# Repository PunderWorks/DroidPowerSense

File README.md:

# DroidPowerSense

An inline battery power switch, protection and telemetry board for droid builds. It sits between the
battery and the rest of the droid, switches the main power from a small remote switch, protects the
droid's electronics, and reports battery voltage and current over CAN FD and UART.

## What it does

- **Power switch with zero drain.** Back-to-back MOSFETs under an LM5060 controller switch up to
  30 A continuous (60 A peak). A small remote switch turns the droid on and off;
  with the switch off, the fitted battery draws nothing beyond semiconductor leakage (< 1 µA).
- **Works with common droid batteries:** 9-32 V, for example 12 V lead-acid, 18 V / 20 V Max
  power-tool packs, and 24 V LiPo / LiFePO4.
- **Protection:** reverse battery, input and output surge (TVS), motor flyback, under- and
  over-voltage cutoff, and an overcurrent / short-circuit trip. The turn-on is soft-started so large
  motor-controller capacitors don't cause a current spike.
- **Telemetry:** battery voltage (readable even with the load switched off), load voltage and
  current (±164 A range, 5 mA resolution), reported over **CAN FD** (daisy-chainable) and a
  level-shifted **UART** (3.3 V or 5 V).
- **Lit remote switches:** supports plain switches and switches with a built-in light that is on
  whenever the droid is on. Firmware can blink it.
- **Two-circuit droids:** a circuit ID jumper lets two boards (one per circuit) identify themselves.
- **Serviceable:** the ESP32-C5 module plugs into sockets and programs over its own USB-C.

## How it fits in a droid

```
Battery ── XT60 lead with in-line blade fuse (30 A) ─▶ BAT IN [ DroidPowerSense ] LOAD OUT ─▶ droid fuse box ── motor controllers / electronics
                                                          │      │     │
                                         remote switch ───┘      │     └── CAN FD in / out (daisy chain)
                                                                 └──────── UART (3.3 V or 5 V)
```

- **Use an XT60 battery lead with an in-line blade fuse** (a common off-the-shelf part) between the
  battery and BAT IN: **30 A** for most builds, 40 A at most. The board is an electronic circuit
  breaker, not a current limiter, so only a fuse clears a dead short quickly. Fused at the battery,
  everything after it is covered: the battery lead, the board, and the remote-switch lead.
- **Wire the remote switch with 22 AWG or heavier.** Its `BAT+` wire carries battery voltage, so a
  chafed lead must draw enough current to blow the battery fuse before the wire overheats; 26 AWG can
  melt first.
- A fuse box for the droid's branch circuits can go after LOAD OUT as usual.
- Up to **4.7 mF** of capacitance on LOAD OUT at 32 V (more at lower battery voltages).
- One board per power circuit.

## Specifications

| | |
|---|---|
| Input voltage | 9-32 V (hardware under-voltage cutoff ≈ 7.5 V, over-voltage cutoff ≈ 38 V) |
| Current | 30 A continuous, 60 A peak |
| Power connectors | XT60PW-M in (mates with the battery's female XT60), XT60PW-F out |
| Off-state drain | < 1 µA with the remote switch open |
| Current / voltage sensing | TI INA237 on a 1 mΩ shunt: ±164 A range, 5 mA resolution; also measures the LOAD OUT voltage |
| Battery voltage sensing | ESP32-C5 ADC through a ÷ 11 divider |
| MCU | Waveshare ESP32-C5-Zero-M (Wi-Fi 6, BLE 5, CAN FD), on 2.54 mm sockets |
| Comms | CAN FD (TI TCAN334G, 2 × 3-pin JST-XH with bus ground, jumper termination); UART (3-pin JST-XH with ground, 3.3 V / 5 V) |
| Board | 76 × 58 mm, 4 layers, 1.6 mm, 1 oz copper, components on one side |
| Mounting | 4 × M3 holes |

## Connectors and jumpers

Every connector has its pin functions printed on the board next to each pin.

| Ref | Silkscreen | Type | Pins / settings |
|---|---|---|---|
| J1 | BAT IN | XT60PW-M | + / − from the battery, through the in-line fused XT60 lead |
| J2 | LOAD OUT | XT60PW-F | + / − to the droid |
| J3 | REMOTE SW | JST-XH 4-pin | `BAT+`, `SW`, `LED-`, `LED+` (see below) |
| J5 / J6 | CAN IN / CAN OUT | JST-XH 3-pin | `GND`, `CANL`, `CANH`; wired in parallel, so IN and OUT are a cabling convention. `GND` is a bus ground reference: run it through every CAN cable |
| J8 | UART | JST-XH 3-pin | `GND`, `RX` (into the board), `TX` (out of the board). Connect `GND` to the other device's ground |
| J7 | TERM | 2-pin jumper | Fitted = 120 Ω CAN termination. Fit only on the boards at the two ends of the bus. |
| J9 | UART V | 3-pin jumper | `3V3`-`UART` = 3.3 V UART; `UART`-`5V` = 5 V UART |
| J4 | CIRCUIT ID | 2-pin jumper | No jumper = circuit 1, jumper on = circuit 2 |

The three jumper shunts (Würth 60900213421) are in the BOM.

The CAN and UART `GND` pins are signal references, not power returns: each goes to the board's
ground through a resettable fuse (PTC), so if a battery-negative lead comes off while a comms cable
is still plugged in, the fuse trips instead of the load current flowing through the thin comms wire.
Always connect battery negative through the XT60s.

### Wiring the remote switch (J3)

| J3 pin | Plain switch | Lit switch, 3-terminal (+ / ACC / GND) | Lit switch, separate LED terminals |
|---|---|---|---|
| `BAT+` | one side | + | one contact |
| `SW` | other side | ACC (output) | other contact |
| `LED-` | — | GND | LED − |
| `LED+` | — | — | LED + |

- **3-terminal lit switches** power their light from the battery, so buy one rated for your pack
  (12 V for lead-acid; 24 V or "12-24 V" for 18-24 V packs).
- **Switches with separate LED terminals:** buy the **5 V or 6 V** LED version. The board powers it
  from its own 5 V, so the same switch works on any battery.

## Before you power it up

- **Fuse the battery lead:** an XT60 lead with an in-line blade fuse (30 A, 40 A max) ahead of
  BAT IN, and 22 AWG or heavier for the remote-switch lead.
- **Heatsink for high continuous current:** typical droid loads (under about 1 A average, with
  short motor peaks) need none. For continuous loads above about 15 A, fit a small stick-on
  heatsink to the marked area on the back, but **only with an electrically insulating thermal pad**. Bare
  metal would short the power nets underneath and bypass the switch.
- **Secure the module** in a droid that vibrates: a dab of hot glue or a cable tie at the antenna end.
  It stands about 11 mm tall on its sockets.
- **Firmware is part of the protection.** Overcurrent cutoff between 30 A and the hardware trip
  point, and never cutting power while the motors are regenerating, are firmware's job; see
  [docs/firmware-requirements.md](docs/firmware-requirements.md).

## Project status

| Area | Status |
|---|---|
| Hardware design | Complete and reviewed: all design and layout checks pass, power stage verified in simulation |
| PCB | v1.0 routed and reviewed for fab: 76 × 58 mm on 4 layers (moved from 70 × 50 mm on 6 layers, cheaper to fab) with 3-pin CAN/UART connectors. DRC and all design checks clean; fab files in [`PCB/production/`](PCB/production/). The renders above are of the earlier 6-layer layout until they are re-rendered. |
| Firmware | Not started (Rust on the ESP32-C5). Requirements captured in [docs/firmware-requirements.md](docs/firmware-requirements.md). |
| Bench testing | Not started. The first-board checklist is in [PCB/README.md](PCB/README.md#bench-checklist-first-board). |

## Repository layout

| Path | Contents |
|---|---|
| [`PCB/README.md`](PCB/README.md) | Hardware design: requirements, circuit, decisions, layout, accepted risks and bench checklist |
| [`PCB/stackup/`](PCB/stackup/) | The electrical design in [Stackup](https://github.com/stackup-eda/stackup) KDL (`board.kdl`, `parts.kdl`); there are no KiCad schematics |
| `PCB/DroidPowerSense.kicad_pcb` | The KiCad 10 board, synced from the Stackup design |
| [`PCB/production/`](PCB/production/) | Fab files: Gerbers and drills, purchasing BOM, placement file |
| [`PCB/datasheets/`](PCB/datasheets/) | Manufacturer datasheets, with source and hash in `manifest.json` |
| [`PCB/libraries/`](PCB/libraries/) | Custom footprints and 3D models (XT60PW, socketed ESP32 module) |
| [`scripts/spice/`](scripts/spice/README.md) | ngspice simulations of the power switch and UART level shifters, and an SOA checker |
| [`docs/firmware-requirements.md`](docs/firmware-requirements.md) | What the firmware must do for the hardware, pin map and peripheral setup |
| `ci/` | The pinned Stackup CLI and the PCB sync check used by CI |
| `src/` | Firmware (Rust, ESP32-C5), not started yet |

## Working on the design

The design is checked with the Cargo-pinned Stackup CLI and KiCad 10 (`kicad-cli`):

```sh
cargo run --locked --manifest-path ci/stackup/Cargo.toml -- check PCB/stackup/board.kdl --locked
python3 scripts/spice/power_switch_sim.py     # power switch, all scenarios
python3 scripts/spice/uart_shifter_sim.py     # UART level shifters
python3 scripts/spice/test_soa.py             # SOA checker unit tests
```

- After any change to the KDL, sync the PCB from Stackup (see [PCB/README.md](PCB/README.md)) and
  commit the board with the KDL. CI fails if they drift apart.
- Refill the pours and regenerate `PCB/production/` after any board change; the commands are in
  [PCB/README.md](PCB/README.md).
- Changes go through pull requests; history is kept linear (rebase merges).

## Ordering

- **Fab:** 4 layers, 1.6 mm, 1 oz copper; minimum track and spacing 0.2 mm. 2 oz outer copper
  roughly doubles the price and isn't needed for typical droid loads; see
  [PCB/README.md](PCB/README.md) for the trade-off.
- **Parts:** the BOM lists Mouser and DigiKey numbers (LCSC where available). The XT60 connectors
  (Amass) and the ESP32-C5-Zero-M module (Waveshare) come from their own channels.
- **Hand assembly:** the connectors, jumpers, module sockets and module are through-hole and
  hand-soldered; the placement file lists only the 69 surface-mount parts.

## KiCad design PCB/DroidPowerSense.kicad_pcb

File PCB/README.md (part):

# DroidPowerSense hardware

The electrical design is Stackup KDL in [`stackup/`](stackup/) (`board.kdl`, plus the local parts in
`parts.kdl`). The KiCad board `DroidPowerSense.kicad_pcb` is synced from it through
`DroidPowerSense.stackup_sch`. Manufacturer datasheets are in [`datasheets/`](datasheets/), with
their source URLs and hashes in `datasheets/manifest.json`.

```sh
stackup check PCB/stackup/board.kdl --locked     # check the design
stackup bom PCB/stackup/board.kdl --locked -o bom.csv
python3 scripts/spice/power_switch_sim.py          # power-switch SPICE corners (23 checks)
```

After changing the KDL, use **Sync PCB from stackup** in KiCad's PCB editor, or sync headless with
the board closed:

```sh
/Applications/KiCad/KiCad.app/Contents/Frameworks/Python.framework/Versions/Current/bin/python3 \
  <stackup checkout>/kicad-plugin/sync_headless.py PCB/DroidPowerSense.kicad_pcb
```

Commit the synced PCB with the KDL. CI fails if syncing would change the committed PCB.

## Requirements

| Area | Requirement |
|---|---|
| Position | Inline between the battery and the droid, before its fuses. One board per circuit; droids with two circuits use two boards. |
| Batteries | 9-32 V: 12 V lead-acid, 18 V / 20 V Max power-tool packs, 24 V LiPo / LiFePO4. |
| Current | < 1 A to 30 A continuous, 60 A peak, measured in both ranges. |
| Power connectors | Polarized, high-current: XT60PW-M in (mates with the battery's female XT60), XT60PW-F out. |
| Switching | MOSFET switch so a fitted battery draws nothing while the droid is off. Switched by a remote low-power switch on a 4-pin JST-XH (switch + lit-switch LED). |
| Lit switch | Support lit-when-on switches: 3-terminal (+ / ACC / GND) and separate-LED-terminal types. The light is on whenever the board is on, firmware can blink it, and it adds no off-state drain. |
| Protection | Reverse polarity, input/output TVS, output flyback diode, over/under-voltage, overcurrent/short trip. |
| Upstream fuse | **Required:** an XT60 battery lead with an in-line blade fuse (30 A, 40 A max) ahead of J_PWR_IN, and the remote-switch lead in 22 AWG or heavier. The LM5060 is a circuit breaker with a 0.3-0.65 s fault delay, not a current limiter: only the fuse clears a dead short, and it backs up sustained overloads. |
| Overcurrent | **Firmware is the primary overload protection:** INA237 ALERT (IO4) set to the over-current limit, firmware asserts PWR_CUTOFF. The LM5060 V_DS trip (~45 A hot / ~105 A cold) is the hardware backstop; between 30 A and the trip point the hardware alone does not open the switch. |
| Load capacitance | Up to 4.7 mF on LOAD OUT at 32 V (Q1 stays within its SOA during turn-on; larger banks at 32 V exceed it). |
| MCU | ESP32-C5 (CAN FD + firmware) on a plug-in module (sockets), serviceable and programmable in place over its USB-C. Firmware in Rust. |
| Comms | CAN FD (two 3-pin JST-XH for daisy-chain, jumper termination), UART (3-pin JST-XH, 3.3 V / 5 V jumper). Pin 1 of each is a ground reference, tied to board GND through a PTC so it can never carry the load's return current. |
| Circuit ID | Firmware must tell circuit 1 from circuit 2. |
| Board | 76 × 58 mm, 4 layers, 1 oz copper, with three layers for the high-current path and a solid ground plane, components on one side. Back-side area for a user-fitted heatsink, recommended above about 15 A continuous. |
| Sourcing | Mouser and DigiKey first; LCSC numbers recorded but JLCPCB is not the planned assembler. |

## Circuit

| Block | Parts | Notes |
|---|---|---|
| Power in/out | J_PWR_IN (XT60PW-M), J_PWR_OUT (XT60PW-F), D_TVS_IN (SMCJ33CA), D_TVS_OUT (SMBJ33CA), D_FLY (B560C) | Bidirectional TVS on both sides; D_FLY clamps inductive kick from motors on the output. |
| Remote switch | J_SW (JST-XH 4-pin), D_SW (B160) | J_SW 1-2 connects VBAT_IN to VSW_CTRL. Open = the only path from the battery is TVS/MOSFET leakage (< 1 µA). D_SW blocks reverse polarity into the control rail. |
| Lit switch | J_SW.3/.4, Q_LED (BSS138), R_LED_PU 10 k | J_SW.4 = +5V for separate-terminal LEDs; J_SW.3 = LED return, switched to GND by Q_LED. R_LED_PU holds the gate on from +3V3, so the light is on as soon as the board is; IO12 low turns it off (blink). |
| High-side switch | U_PROT (LM5060), Q1/Q2 (CSD18532Q5B, back-to-back, 2.5 mΩ each), R_GATE, D_GOFF, C_GATE (100 nF 100 V), R_GATE_C (1 k), Q_REV + D_REV + R_REV | Common-source back-to-back N-FETs so the switch blocks both directions. Q_REV clamps V_GS during reverse polarity (LM5060 Fig. 41). C_GATE + R_GATE_C slows the output (~240 V/s typ) to limit inrush into capacitive loads. C_GATE is sized against the start-up timer: worst case at 32 V the gate needs 0.25 s and the timer allows 0.48 s (LM5060 IGATE 17 µA, VGATE-TH 6.5 V, ITIMERL 7 µA, VTMRH 1.70 V, ±10 % parts). 220 nF needed 0.55 s and could latch a start-up fault. |
| Protection thresholds | R_SENSE 33 k, R_OUT 10 k, C_TIMER 2.2 µF, UVLO 33 k/10 k, OVP 180 k/10 k | V_DS trip ~528 mV across 5 mΩ ≈ 105 A cold / ~45 A at 100 °C (clears 30 A continuous rating); UVLO ≈ 7.5 V rising; OVP ≈ 38 V; C_TIMER 2.2 µF: start-up window ≥ 0.48 s, V_DS fault delay 0.34 s typ / 0.65 s max. |
| MCU cutoff | Q_CUTOFF (BSS138), R_CUTOFF_PD 100 k | Firmware drives PWR_CUTOFF high to pull LM5060 EN low: load off, MCU stays powered from VSW_CTRL to report the fault. Pull-down keeps the load on through MCU boot/reset. |
| Sensing | R_SHUNT (CSS2H-2512R-1L00F, 1 mΩ 5 W), U_INA (INA237), C_INA_VS | INA237: 85 V common-mode/VBUS (VOUT reaches 42 V before D_TVS_OUT conducts, 53 V clamped; the INA226's limit was 40 V). ADCRANGE 0: ±163.84 A at 5 mA/LSB; offset ±50 mA, gain ±0.3 % max. A0/A1 to GND: I²C address 0x40. Shunt 0.9 W at 30 A, 3.6 W at 60 A (short-time overload 25 W for 5 s). Bus voltage measured on VOUT. |
| Battery ADC | R_VBAT_TOP 100 k / R_VBAT_BOT 10 k, C_VBAT_ADC | VSW_CTRL ÷ 11 into IO6, so battery voltage is readable with the MOSFETs off. |
| 5 V | U_BUCK (LMR14030, 4-40 V), R_BUCK_IN 3.3 Ω, L_BUCK 10 µH, D_BUCK (B360A) | 400 kHz, FB 56.2 k/10 k → 4.97 V. Feeds the module's 5 V pin and the UART 5 V option. R_BUCK_IN with C_BUCK_IN1/2 (BUCK_VIN) low-passes the buck input (~66 µs, ~25 µs after X5R DC-bias loss): VSW_CTRL can reach 37-53 V in an input surge, above the LMR14030's 44 V VIN/EN absolute maximum. Drop 0.76 V / 0.17 W at the worst load (0.23 A at 9 V). R_BUCK_EN pulls EN from BUCK_VIN. |
| MCU | U_MCU (Waveshare ESP32-C5-Zero-M), J_MCU_L/J_MCU_R sockets | The module plugs into two 1x9 sockets. The module's own buck makes +3V3 for the carrier (pin 3). USB-C on the module is the programming path. The module has both an onboard ceramic antenna (J2, OA-W03) and an IPEX-1/U.FL connector (J3), chosen by an RF switch on internal GPIO26 (ANT_Ctrl, 200 k pull-up to 3V3; module schematic). Firmware must drive GPIO26 to select the onboard antenna. No U.FL-free variant exists (the -M SKU only adds headers). |
| CAN FD | U_CAN (TCAN334GDR), J_CAN1/J_CAN2, R_TERM + J_TERM, F_CAN_GND | 3.3 V transceiver, normal mode (STB/SHDN internal pull-downs). Connectors: pin 1 CAN_GND, 2 CANL, 3 CANH. CAN_GND runs straight from J_CAN1 to J_CAN2 (the bus ground daisy-chains) and reaches board GND through F_CAN_GND (see Comms ground pins below). |
| UART | J_UART, J_VIO, Q_TX/Q_RX (BSS138) + pull-ups, F_UART_GND | ESP32-C5 pins are not 5 V tolerant, so both directions are level-shifted. J_UART: pin 1 UART_GND (to GND through F_UART_GND), 2 RX, 3 TX. |
| Circuit ID | J_CIRCUIT, R_CIRCUIT_PU | Open = circuit 1, shorted = circuit 2. |
| Indicator | D_PWR_LED + 1 k | On when +3V3 is up (remote switch closed). |

Jumpers: **J_VIO** (silkscreen "UART V") 1-2 = 3.3 V UART, 2-3 = 5 V UART. **J_TERM** (silkscreen "TERM")
fitted = 120 Ω terminator.
**J_CIRCUIT** no jumper = circuit 1, jumper on = circuit 2. The three shunts are in the BOM
(SH_VIO / SH_TERM / SH_CIRCUIT, Würth 60900213421) as BOM-only parts with outline-only footprints.

**Not in the BOM (user-supplied):** the heatsink (recommended above about 15 A continuous) and its electrically insulating thermal
pad (see Layout), M3 mounting hardware, and the upstream battery fuse.

Silkscreen convention: every JST connector has its pin functions printed in line with each pin
(J3 `BAT+`/`SW`/`LED-`/`LED+`, J5/J6 `CANH`/`CANL`/`GND`, J8 `GND`/`RX`/`TX`), not pin numbers. J5 is marked CAN IN and J6
CAN OUT (vertical text beside their pin labels); they are wired in parallel, so the marking is a cabling convention, not a direction the bus
needs. The labels sit over the tracks that run into each pin, which prints legibly over soldermask.

## Remote switch wiring (J3)

| J3 pin | Silkscreen | Net | Plain switch | 3-terminal lit switch (+ / ACC / GND) | Separate-LED-terminal switch |
|---|---|---|---|---|---|
| 1 | `BAT+` | VBAT_IN | one side | + | one contact |
| 2 | `SW` | VSW_RAW | other side | ACC (output) | other contact |
| 3 | `LED-` | SW_LED_K (Q_LED drain) | — | GND | LED − |
| 4 | `LED+` | +5V | — | — | LED + |

- **3-terminal switches** light their LED from the battery, so buy one rated for the pack (12 V for
  lead-acid, 24 V or "12-24 V" for 18-24 V packs). Their LED also sees the full reverse voltage if the
  battery is reversed; that relies on the switch's own protection.
- **Separate-terminal switches**: buy the **5 V or 6 V LED** version. It runs from the board's 5 V, so
  the same switch suits every battery from 12 V to 32 V.
- Battery pins (1-2) are at one end, so a slipped wire can short BAT+ to SW (just turns the board on)
  but never puts the battery on +5V.

## GPIO table (Waveshare ESP32-C5-Zero)

Firmware-side requirements (overcurrent cutoff, regen rule, INA237 setup, antenna select) are in
[docs/firmware-requirements.md](../docs/firmware-requirements.md).

| GPIO | Net | Function | Notes |
|---|---|---|---|
| IO0 | PWR_PGOOD | LM5060 nPGD (open drain) | 10 k pull-up. |
| IO1 | PWR_CUTOFF | Load cutoff | High = load off. 100 k pull-down. |
| IO2 | I2C_SDA | INA237 | 4.7 k pull-up. Strapping pin MTMS (SDIO edge only; harmless). |
| IO3 | I2C_SCL | INA237 | 4.7 k pull-up. Strapping pin MTDI (SDIO edge only; harmless). |
| IO4 | INA_ALERT | INA237 ALERT (open drain): firmware over-current cutoff | 10 k pull-up. |
| IO5 | UART_TX_3V3 | UART TX | Via Q_TX to J_UART.3. |
| IO6 | VBAT_ADC | ADC1 | Battery ÷ 11. |
| IO7 | CIRCUIT_ID | Input | 10 k pull-up. Strapping pin for JTAG source, only read if EFUSE_JTAG_SEL_ENABLE is burnt (default not). |
| IO8 | CAN_TX | TWAI/CAN FD TX | |
| IO9 | CAN_RX | TWAI/CAN FD RX | |
| IO10 | UART_RX_3V3 | UART RX | Via Q_RX from J_UART.2. |
| IO11 | — | U0TXD | Left free for the ROM boot log. |
| IO12 | SW_LED_EN | Lit-switch LED (Q_LED gate) | 10 k pull-up: light on by default; drive low to blink. U0RXD, not a strapping pin (ESP32-C5 datasheet p. 27); input with weak pull-up at reset (p. 20). The J_UART port is unaffected: it uses UART1 on IO5/IO10. |
| IO13/IO14 | — | USB D-/D+ | Module USB-C. |

## Layout

**76 × 58 mm**, 4 layers (F.Cu parts and routing / In1.Cu solid GND / In2.Cu power pours, +3V3 pour
and VSW_CTRL routing / B.Cu heatsink copper, GND and short routes), all parts on the top side.
`scripts/layout_4layer.py` converted the hand-placed 70 × 50 mm 6-layer layout: it moved parts and
silkscreen by region, rebuilt the outline, pours and stitching vias, and deleted the old routing.
Signals were then routed by hand in KiCad; the script refuses to run on anything but the 6-layer
board, so it can't overwrite the routing. GND stitching and the decoupling-cap ground vias come from
`scripts/stitch_gnd.py` (see Pours below). The DRC's `silk_edge_clearance` check is set to ignore because the
J1/J2 XT60 silkscreen overhangs the board edge by design; check any new edge-mounted part by eye.

```
 ┌────────────────────────────────────────────────────────────────────────┐
 │ J1 XT60 │D1│ Q1 │ Q2 │ R13 │ D6 │ D5 │ J2 XT60   power row (y 0-19)        │
 │  in     ├──┴─ gate clamp, LM5060, INA237 ──┤  out                         │
 │ ○ PWR LED, dividers               CIRCUIT ID   ○                         │
 │ J3 switch │ ESP32-C5-Zero-M │ VIO  U5 CAN  TERM   J5 CAN IN              │
 │ buck      │ on sockets,     │ level shift   F1    J6 CAN OUT             │
 │ ○         │ antenna at edge │ F2  J8 UART          ○                     │
 └────────────────────────────────────────────────────────────────────────┘
```

- **XT60 overhang.** Both XT60PW bodies overhang the side edges by about 5 mm; the pins and both
  support pegs stay on the board (the datasheet land pattern fixes only the pins and the pegs 6 mm in
  front of them). This is what lets D_TVS_IN, Q1, Q2, R_SHUNT, D_TVS_OUT and D_FLY fit in one row
  between the connectors (0.2-0.4 mm between courtyards). DRC's silk-to-edge warnings on J1/J2 are
  this overhang.
- **ESP32 on sockets.** U_MCU is the ESP32-C5-Zero-M (headers pre-soldered) in two 1x9 sockets
  (J_MCU_L/J_MCU_R, Sullins PPPC091LFBN-RC, 8.5 mm). The module sits ~11 mm up, so the USB-C plug
  clears everything, low parts sit under the module (pull-ups, cutoff FET, ADC divider), and the
  module can be swapped. The sockets are pinless BOM parts: their pins use U_MCU's holes. They carry KiCad's stock
  1x09 socket 3D model (the module's STEP already includes its own headers), so the 3D view shows the
  full stack. The antenna
  end keeps its all-layer copper and footprint keep-out at the bottom edge.
- **Logo:** `DroidPowerSense:PunderWorks_Logo_10mm` / `_14mm` / `_18mm` are board-only silkscreen
  footprints (no pads, excluded from BOM and placement), generated by `scripts/make_logo_footprint.py`
  from `libraries/logos/PunderWorks-black.png`. Minimum stroke 0.31 / 0.44 / 0.56 mm. Place from the
  footprint library; flip to put it on the back. Regenerate another size with
  `python3 scripts/make_logo_footprint.py PCB/libraries/logos/PunderWorks-black.png <width_mm> <out.kicad_mod>`.
- **Mounting holes:** four M3, at the bottom corners and on the side edges just below the XT60s (the
  top corners are under the connectors).
- **Heatsink area (back, 43 × 16 mm under D_TVS_IN … D_FLY).** The back copper there is the
  VBAT_IN / VSW_OUT / VOUT pours plus GND, under soldermask, tied to the top pours by stitching vias.
  No through-hole tails land in it. A stick-on heatsink is recommended for continuous loads above
  about 15 A (see FET heat below) and must go on with an **electrically insulating** thermal pad or
  tape: bare metal would short the three power nets and bypass the switch.
  The area is marked with corner brackets and a note on B.SilkS.
- **5 V buck (U_BUCK, bottom left)** follows the LMR14030 layout example (datasheet §7.4.1,
  Fig. 7-10 on p. 23). The input caps stand left of U_BUCK with their + pads level with VIN (pin 2)
  and their GND pads up. D_BUCK lies flat above the IC, its cathode over SW (pin 8) and its anode
  over the input caps' ground. L_BUCK stands upright beside D_BUCK's cathode with its output pad up
  next to the output caps, which sit above D_BUCK. All of their ground pads, U_BUCK pin 7 and the
  SS/RT/FB parts share one top-side GND area. That area ties to the plane at the output-cap ground
  (two vias, at C_BUCK_OUT1/2) and through U_BUCK's thermal-pad vias; the input caps
  deliberately have no vias of their own, so the switching current stays on the top-side ground.
  Keep it that way if the buck is re-routed. The feedback divider sits at the FB pin.

**Fab spec: 1.6 mm, 4 layers, 1 oz copper on all layers** (0.245 mm prepreg, 0.95 mm core in the
board file; the fab sets its own stackup). v1 was ordered this way from PCBWay (2026-11-10). 2 oz
outer copper doubled the price, and a droid's average load is under 1 A, with 30 A continuous a rare
ceiling. On the 30 A path, 1 oz against 2 oz outer copper (estimates from copper sheet resistance
and IPC-2221, not measured):

| | 2 oz outer | 1 oz outer |
|---|---|---|
| Power-path copper resistance | 0.31 mΩ | 0.51 mΩ |
| Copper heat at 30 A | 0.27 W | 0.46 W |
| Narrowest section (VSW_OUT) | 1.51 mm² | 0.90 mm² |
| Q1-Q2 link (VSW_MID) | 0.06 mΩ | 0.12 mΩ |

The copper carries 30 A either way: the extra ~0.2 W is small next to the FETs' 5-8 W. What 1 oz
loses is heat spreading around Q1, Q2 and R_SHUNT, which is why the heatsink is recommended for
sustained high current. Order 2 oz outer only if bench step 6 shows the board runs too hot at the
loads it will really see.

Pours (added by `scripts/layout_4layer.py`):
- VBAT_IN, VSW_OUT and VOUT on F.Cu, In2.Cu and B.Cu along the power row (y 44.4-55.6, about 11.2 mm
  tall), priority 3, pads connected solidly; 183 stitching vias (0.8 / 0.4 mm, 1.27 mm grid, kept
  0.4 mm off every pad). The 11.2 mm row was sized so three layers with 2 oz outer copper
  (2 + 1 + 2 oz) matched the 6-layer board's four layers × 8.7 mm. With the 1 oz copper ordered, the
  narrowest cross-sections as routed are VBAT_IN 1.18 mm², VSW_OUT 0.90 mm², VOUT 1.18 mm² (1.96,
  1.5 and 1.96 mm² at 2 oz outer). Each of the Q1/Q2 drain tabs and
  R_SHUNT pads has 5-12 of these vias within 2.5 mm to carry the current between layers.
- VSW_MID (Q1 sources to Q2 sources) is F.Cu only, across the 0.95 mm gap between the two rows of
  source pins; the gap is too narrow for a via. **Nothing may be routed through that gap.** The
  GATE_FET link from Q1's gate (top of its row) to Q2's gate (bottom of its row) goes around the
  outside of Q2's source pins instead, leaving the gap as solid copper about 3.9 mm wide
  (~0.06 mΩ). An earlier route ran the gate track down the gap and left 0.11 mm² for the full load
  current (~270 A/mm² at 30 A); the 2026-11-09 review caught it.
- Ground planes (priority 0) on all 4 layers: In1.Cu is the solid reference plane. J1/J2
  GND pins and the D1/D5/D6 GND pads connect solidly (thermal spokes would choke 30 A); the XT60 GND
  pins need a large iron to hand-solder.
- GND stitching and decoupling vias (0.6 / 0.3 mm, tented) come from `scripts/stitch_gnd.py`: a
  2.5 mm grid wherever a via fits wholly inside the GND fill on F.Cu, In1.Cu and B.Cu (clear of the
  In2 power pours, courtyards, the antenna keep-out, the QR code and the logos), at least two vias on
  every F.Cu GND island, and a via with a short track at each ground pad in its `PAD_VIAS` list
  (C_PROT_VIN, C_INA_VS, the TCAN334G's VCC cap and GND pin, and the buck output caps). Refill the
  zones, run it with KiCad's Python, refill again. It skips spots near existing GND vias, so it is
  safe to rerun after routing changes.
- In2.Cu is the internal signal layer (referenced to the In1.Cu GND plane). It carries the power-row
  pours, a +3V3 pour (priority 1) under the module, CAN and UART (y 61.5 to the bottom edge, x ≥ 76.2),
  and a GND fill elsewhere. VSW_CTRL runs on it as 0.35-0.5 mm tracks (LM5060, dividers, buck input),
  not a pour. Keep In2 tracks short where they cut the +3V3 pour; +3V3 can also run as Power-class
  tracks on F.Cu.

Net classes (Board Setup → Net Classes, assigned by net-name pattern in `DroidPowerSense.kicad_pro`):

| Class | Track | Clearance | Via | Nets |
|---|---|---|---|---|
| HighCurrent | 3.0 mm | 0.2 mm | 0.8 / 0.4 | VBAT_IN, VSW_MID, VSW_OUT, VOUT |
| Power | 0.5 mm | 0.2 mm | 0.6 / 0.3 | GND, VSW_CTRL, VSW_RAW, +5V, +3V3, BUCK_SW, UART_VIO, CAN_GND, UART_GND |
| GateDrive | 0.3 mm | 0.2 mm | 0.6 / 0.3 | GATE_FET, GATE_DRV, REV_BASE |
| CAN | 0.35 mm | 0.2 mm | 0.6 / 0.3 | CANH, CANL, Net-(J7-A) |
| Default | 0.25 mm | 0.2 mm | 0.6 / 0.3 | all other signals |

Stackup 0.3.0 doesn't derive net classes, so these are plain KiCad classes (no `stackup:` prefix)
and the sync leaves them alone. Expected exceptions when routing: the HighCurrent nets' thin
branches (Kelvin sense to U2, VBAT_IN sense to R4 R_SENSE, the VSW_MID spur to the reverse clamp; all carry
mA or less) and neck-downs where Power tracks meet the 0.5 mm-pitch pins of U1 and U2.
0.2 mm clearance is well above what 32 V needs.

`scripts/layout_4layer.py` made this layout from the 70 × 50 mm 6-layer one; the board file is now
the source of truth. `scripts/layout_compact.py` (70 × 50 mm, 6 layers) and `scripts/layout_pcb.py`
(90 × 66 mm, 4 layers) are kept for their helpers and history; their reference designators no longer
match the board.

**Why 4 layers at 76 × 58 mm (2026-11-09).** At 70 × 50 mm the board needed 6 layers: 4 layers
there could not be routed cleanly, because the band under the power row (gate clamp, LM5060,
INA237, dividers) is where every left-to-right signal crosses, and the power row blocks every layer
above it. The 6-layer board used only F.Cu, In2.Cu and B.Cu for signals; In3.Cu (+3V3 plane and a
fourth power pour) and In4.Cu (second GND plane) were planes. Going to 4 layers loses one 1 oz
power layer (made up by an 11.2 mm instead of 8.7 mm power row), the +3V3 plane (now an In2 pour
and tracks) and some heat spreading (partly made up by 26 % more board area). The extra 6 mm of
width spreads the gate-drive cluster and the CAN/UART column; the extra 8 mm of height goes to the
power row (2.5 mm), the routing band below it (3 mm) and the bottom edge (2.5 mm). 76 × 58 is
about 52 % component density, against ~65 % at 70 × 50; going below about 74 × 56 brings back the
routing problem, and above 80 × 60 the board is bigger than it needs to be. The 90 × 66 mm 4-layer
original was larger than needed because its parts were not yet compacted (module on sockets with
parts under it, XT60 overhang).

Status (2026-11-09): routed on 4 layers. DRC (all severities, zones refilled) 0 violations / 0
unconnected; `stackup check` 84 parts / 48 nets, 0/0/0; PCB sync clean. 433 tracks, 312 vias (101
GND). Minimum track width is 0.25 mm and minimum clearance 0.2 mm; the 0.5 mm-pitch U1/U2 pads
have 0.2 mm gaps. 0.2 mm / 0.2 mm is within standard 1 oz rules.

**Fab files** are in [`production/`](production/): Gerbers + job file (1.6 mm) and PTH/NPTH
drills with maps in `production/gerbers/`; the purchasing BOM (`stackup bom`) and the placement file in
`production/bom/`. The placement file lists only assembler-placed parts (69 on the 4-layer board): the BOM's hand-soldered
parts (connectors, module, sockets, loose jumper shunts) are left out to match its DNP column. The
sync marks every `hand=#true` footprint *Exclude from position files* and *Exclude from BOM*, so
`kicad-cli` and the PCBWay plugin leave them out on their own.
Regenerate both after any board change. **Refill and save the pours first:** the exporters plot the
fills stored in the board file, and a script or sync that edits copper without refilling leaves stale
fills that would go to the fab (this happened once; the fix was this refill).

```sh
K=/Applications/KiCad/KiCad.app/Contents/MacOS/kicad-cli; B=PCB/DroidPowerSense.kicad_pcb
$K pcb drc --refill-zones --save-board --severity-all -o /tmp/drc.rpt $B   # refill, save, and check
$K pcb export gerbers --board-plot-params -o PCB/production/gerbers/ $B
$K pcb export drill --excellon-separate-th --generate-map --map-format gerberx2 -o PCB/production/gerbers/ $B
$K pcb export pos --format csv --units mm --side both -o PCB/production/bom/DroidPowerSense-pos.csv $B
stackup bom PCB/stackup/board.kdl --locked -o PCB/production/bom/DroidPowerSense-bom.csv
```

## Verification

- `scripts/spice/power_switch_sim.py`: switch open (no drain), turn-on across 9-32 V and V_GS(th)
  corners, MCU cutoff, reverse polarity (-12 to -32 V), capacitive inrush (100 µF to 4.7 mF; the
  slow corner stacks the LM5060 start-up limits with ±10 % C_GATE / C_TIMER and VTMRH 1.70 V),
  hot-FET 30 A continuous margin, overcurrent stall vs dead short, and motor regeneration.
  See [`scripts/spice/README.md`](../scripts/spice/README.md).
- `scripts/spice/uart_shifter_sim.py`: bidirectional BSS138 level shifter verification across 3.3 V
  and 5.0 V VIO, threshold corners, and cable capacitances up to 500 pF.
- `scripts/spice/test_soa.py`: unit tests for the Safe Operating Area and moving-window thermal
  integrator library (`scripts/spice/soa.py`). All 10 tests pass.

## Accepted risks and known gaps

- **Upstream battery fuse is required for dead-short protection.** The LM5060 acts as an electronic
  circuit breaker with a 0.34 s typical (0.65 s worst) fault delay, not a current limiter. A dead short (<10 mΩ) directly on
  the output draws >1000 A from low-impedance lithium batteries, which violates FET single-pulse SOA
  before the LM5060 timer elapses. An upstream fast-acting fuse (30-50 A blade or MIDI fuse) on the main
  battery feed is required to clear dead shorts (<2 ms).
- **The remote-switch lead (J3 `BAT+`) relies on the battery fuse.** `BAT+` is tied straight to
  VBAT_IN; a chafed switch lead shorted to chassis draws ~75-100 A at 32 V through 1 m of thin wire.
  The in-line battery fuse clears that, provided the wire outlasts the fuse: by the Onderdonk
  estimate 26 AWG melts at ~52 A in 0.5 s, 22 AWG at ~133 A, hence 22 AWG or heavier and a fuse no
  larger than 40 A. On-board protection was evaluated and set aside (2026-11-08): small 60 V PTCs
  interrupt only 10-40 A (TE/Littelfuse SMD050F: 10 A at 60 V), and an eFuse before the switch is
  always powered (TI TPS2660: 300 µA on, 20 µA off), which breaks the zero-drain requirement. A v2
  could make the switch lead a low-current control signal instead of battery +.
- **Inrush into capacitive loads.** With no C_GATE, charging large capacitor banks at 32 V produces
  peak currents >120 A. C_GATE = 100 nF limits inrush into 4.7 mF at 32 V to 1.9 A (Q1 at 0.72x SOA at
  the fast corner). 10 mF at 32 V exceeds the SOA (1.4-1.5x); a larger C_GATE needs a larger C_TIMER,
  which lengthens the overload delay, so the board is rated for 4.7 mF at 32 V.
- **Overloads between 30 A and the V_DS trip.** The trip sits at ~45 A hot / ~105 A cold. At 12 V a
  104 A overload (battery-limited) never trips and puts Q1 at 1.1x its 1 s SOA; at 32 V a 117 A
  overload trips after 0.65 s worst case with Q1 at 1.05x. No C_TIMER value fixes this without breaking
  start-up (one timer serves both). Firmware cutoff on INA237 ALERT and the upstream fuse are the
  protection; the simulation reports these cases as failures on purpose.
- **Input surges and the 5 V buck.** D_TVS_IN (SMCJ33CA, `datasheets/SMCJ.pdf` p. 3) has V_BR
  36.7-40.6 V and clamps at 53.3 V max at 28.1 A, rated on the 10/1000 µs waveform (Fig. 4); its
  dynamic resistance is ~0.45 Ω, so VBAT_IN passes the LMR14030's 44 V limit once ~7.5-16 A flows in
  it. R_BUCK_IN (≥ 25 µs with C_BUCK_IN after DC-bias loss) covers the events a battery system
  produces: the battery-lead inductance kick when the FETs open under load (~1 µH × 30 A = 0.45 mJ in
  ~3 µs, ~1 V rise on BUCK_VIN) and hot-plug ringing. A full-energy 1 ms surge on the battery lead
  would charge through it; that needs an external source on the lead (a battery can't push current
  into a 33 V-standoff TVS, and regen with the switch off lands on VOUT, not VBAT_IN).
- **Hot-FET overcurrent threshold margin.** At 100 °C junction temperature, R_DS(on) rises 1.55x.
  With R_SENSE = 22 kΩ and minimum I_SENSE (13.6 µA), the LM5060 will false-trip at 30 A continuous.
  Increasing R_SENSE to 33 kΩ raises the hot threshold to ~45 A, safely clearing 30 A continuous.
- **Motor regeneration into cutoff FETs.** When the FETs are ON, motor regen flows safely back into
  the battery pack (VOUT ~32.7 V). If firmware shuts off the FETs or asserts `PWR_CUTOFF` while motors
  are actively generating, current dumps into D_TVS_OUT (SMBJ33CA), exceeding its continuous pulse
  rating. Firmware policy: never assert cutoff while motors are spinning.
- **High-speed UART over long cables.** The BSS138 passive pull-ups pass timing up to 115.2 kbps on
  cables up to 5 m (500 pF) and up to 1 Mbps on cables under 1.5 m (150 pF). For 1 Mbps over long droid
  wiring harnesses, use the onboard TCAN334G CAN FD transceiver instead.

- **Copper temperature at 30 A is calculated, not measured.** Measure the shunt, FETs and the XT60
  pins at 30 A continuous on the first board (bench step 6).
- **Pre-fab review (2026-11-08).** Placement was generated, routing done by hand. Reviewed: footprints
  against the package drawings (Q1/Q2 use KiCad's TDSON-8-1: pin-compatible with TI's DNK land
  pattern, drain pad ~0.2 mm larger), diode and transistor orientation by net, Kelvin sense routing
  (each U_INA sense track leaves from inside its own shunt pad), DRC, and the SPICE suite.
- **Pre-fab review of the 4-layer board (2026-11-09).** Checked: every pad's net against the
  Stackup design (sync check); the LM5060, INA237, LMR14030 (SO-8) and TCAN334 pin numbers against
  their datasheet pin tables; the ESP32-C5-Zero-M header order against the module schematic
  (pin 17 = IO12/U0RXD, 18 = IO11/U0TXD); transistor and diode pins by net; Kelvin sense (unchanged
  from the 6-layer review); copper cross-sections along the 30 A path; decoupling placement and
  ground vias. Fixed from the review: the GATE_FET track that cut VSW_MID (see Pours), the buck
  layout (its top-side ground was split into five islands joined only through In1, and the catch
  diode sat 6-8 mm from the SW pin; now re-placed after TI's layout example, see Layout), ground
  vias at the LM5060, INA237 and TCAN334G decoupling caps, and C_BUCK_OUT2 moved off the board
  edge (it was 0.4 mm from it, parallel, where depaneling can crack an MLCC). Not changed: the
  ESP32 module's own decoupling is on the module, and the board's C_3V3_1 / C_BUCK_OUT3 sit at its
  3V3 and 5V pins.
- **Comms ground pins (2026-11-09).** J_CAN1/J_CAN2/J_UART pin 1 is a ground reference: UART is
  single-ended and needs one whenever the other end isn't on the same battery (a USB adapter, a
  separately powered board), and a CAN ground wire keeps nodes within the TCAN334G's common-mode
  range and gives CANH/CANL a defined return. Each reaches board GND through a Bourns
  MF-MSMF014/60X-2 PTC (F_CAN_GND, F_UART_GND) so it can't become the load's return path: if this
  board's battery-negative XT60 comes off while a cable stays connected, the return current would
  otherwise flow through a 3 A JST contact and thin signal wire. A plain series resistor can't do
  this (10 Ω would dissipate ~100 W at 32 V). The fault current is bounded by the load current
  (firmware INA237 cutoff ~30 A, 30-40 A fuse), inside the PTC's Imax 40 A at Vmax 60 V
  (`datasheets/MF-MSMF.pdf` p. 1). Rejected: MF-MSMF010/014 without the X suffix (not recommended
  for new designs), MF-MSMF010/60X (barely stocked), and the Bel 0ZCJ0010FF2E 1206 (60 V but Imax
  only 10 A, `datasheets/0ZCJ.pdf`). Signal-reference current is about 1 mA (UART pull-ups), so R1max 6 Ω adds ~6 mV.
  The KiCad 1812 fuse footprint doesn't match Bourns' Style 2 land pattern, so the board uses
  `DroidPowerSense:Bourns_MF-MSMF_1812_Style2` (1.68 × 2.95 mm pads, 3.1 mm gap, p. 7). Stock
  2026-11-09: Mouser 3,560, DigiKey 3,613; not at LCSC. The B3B-XH-A(LF)(SN) has no DigiKey listing
  and Mouser is at 0 with stock on order; LCSC has 175k.
- **Reversed power with CAN/UART grounds connected.** A reversed battery with another board's
  ground connected through a comms cable drives current through that ground pin; the PTC trips and
  limits it to tens of mA (tripped dissipation ~0.8 W, `datasheets/MF-MSMF.pdf` p. 1).
- **PTC fault current above Imax.** With no load resistance at all, 32 V across Rmin 0.40 Ω would be
  80 A, above the 40 A Imax. In practice the load sets the current and firmware and the fuse cap it
  near 30-40 A; a PTC pushed past Imax can fail open.
- **Mounting holes have no MPN** (drill only).
- **J_SW has no DigiKey number.** B4B-XH-A(LF)(SN): Mouser 306-B4BXHALFSN (49,815), LCSC C144395
  (636k), checked 2026-11-08. DigiKey lists only a different plating variant (B4B-XH-A).
- **INA237 stock and accuracy.** INA237AIDGSR: LCSC 9,895, Mouser 27, DigiKey 0 (2026-11-08); the
  pin-compatible INA238 (±0.1 % gain) was out of stock everywhere. Offset ±50 µV
  max is ±50 mA on the 1 mΩ shunt, coarser than the INA226's ±10 mA. Firmware uses the INA237
  register map (not the INA226's).
- **Q_LED is a 50 V part on a node that can see the input TVS clamp.** With a 3-terminal switch and
  the light blinked off, a surge clamped by D_TVS_IN (SMCJ33CA, up to ~53 V at full surge current)
  reaches Q_LED's drain through the switch LED and its resistor, which limit the current. Accepted:
  the window is short and the current small. A 60 V FET would remove it, but 2N7002-class parts
  have V_GS(th) up to 2.5 V, too close to a 3.3 V gate drive.
- **J_SW miswiring:** shorting SW (battery, when on) to LED- while Q_LED is on overloads Q_LED (it
  fails; the board otherwise survives). Shorting LED+ to anything grounded trips the buck's
  current limit and resets the MCU until removed.
- **FET heat at high continuous current, in still air.** Each CSD18532Q5B dissipates ~2.3 W typical
  (2.5 mΩ at 25 °C) to ~3.4 W hot at 30 A, plus ~0.9 W in the shunt: about 5.4-7.7 W on a
  76 × 58 mm board. Heat goes with the square of the current. By a still-air rule of thumb (not
  simulated), the rise above ambient is about:

  | Continuous load | FET + shunt heat | Rise above ambient |
  |---|---|---|
  | 1 A (typical average) | ~6-9 mW | negligible |
  | 10 A | ~0.6-0.9 W | ~10 °C |
  | 15 A | ~1.4-1.9 W | ~20-25 °C |
  | 20 A | ~2.4-3.4 W | ~30-40 °C |
  | 30 A | ~5.4-7.7 W | ~65-90 °C |

  The rule of thumb was worked out for 2 oz outer copper; the 1 oz board spreads heat less well and
  runs somewhat hotter. Hence the guidance: **fit the heatsink for continuous loads above about
  15 A** (held for more than a minute or so). Short peaks such as motor starts and stalls are
  absorbed by the copper's and FETs' thermal mass. Measure FET and shunt temperatures on the first
  board with and without a heatsink (bench step 6) and move the 15 A line to match.
- **XT60 bodies overhang the board edge ~5 mm** (pins and pegs on board). Plug forces go into the
  pins and pegs, which is what they are rated for; the front of the plastic body is unsupported.
- **The module stands ~11 mm tall on 18 socket contacts.** In a vibrating droid, add a dab of hot
  glue or a cable tie at the antenna end.
- **ESP32-C5-Zero-M is bought from Waveshare** (SKU 34598); Mouser, DigiKey and LCSC don't list it
  (checked 2026-11-08). The socket height is confirmed: PPPC091LFBN-RC
  (PP polyester / phosphor bronze, P gold flash, C 0.100", 09 positions, 1 row, LFB straight, N no
  mounting) has a .335" [8.50 mm] insulator and 6.0 mm insertion depth, with a Ø1.02 mm recommended
  hole (`datasheets/Sullins-FemaleHeader.pdf`, catalog p. 114-115; the footprint drills 1.0 mm). The
  ~11 mm module height adds the -M module's own header plastic, which Waveshare doesn't dimension.
- **Reference designators shifted** when Q_LED/R_LED_PU were added (Stackup assigns them in KDL
  order): the UART FETs are now Q6/Q7 and the former R25-R29 are R26-R30.

## Bench checklist (first board)

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
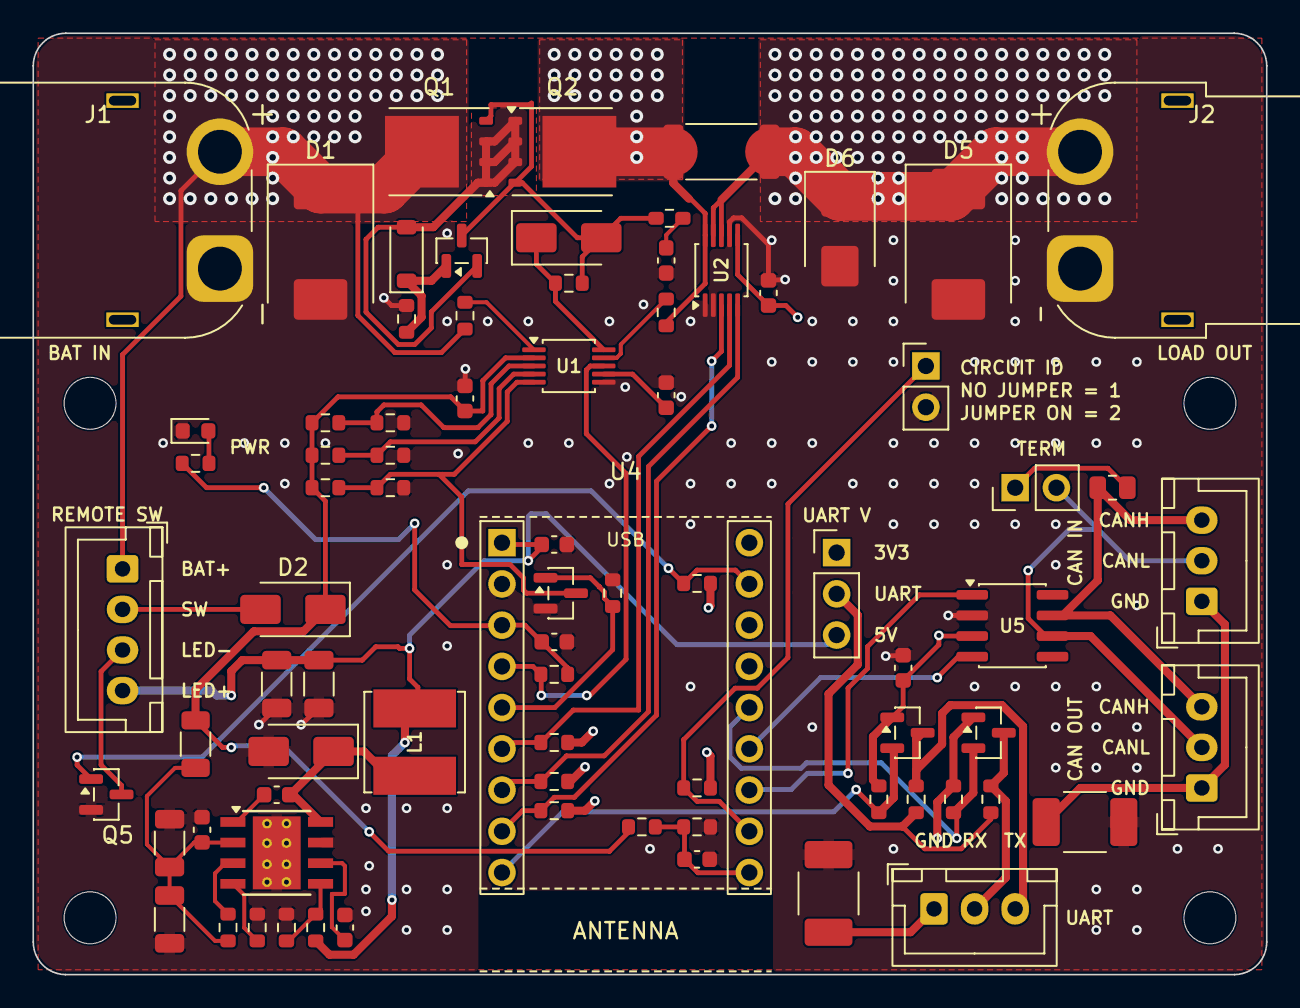
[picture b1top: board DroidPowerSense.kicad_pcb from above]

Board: 4 copper layers, 76.0 x 58.0 mm, 89 parts (1 on the bottom side), 48 nets.

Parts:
C1, C2, C4, C5, C8, C10, C13, C14, C15: 100nF; C_0603_1608Metric
C3: 2.2µF; C_0603_1608Metric
C6, C7, C11, C12: 10µF; C_1206_3216Metric
C9: 10nF; C_0603_1608Metric
D1: SMCJ33CA-13-F; D_SMC
D2, D3: B160-13-F; D_SMA
D4: 1N4148W-TP; D_SOD-123
D5: B560C-13-F; D_SMC
D6: SMBJ33CA-13-F; D_SMB
D7: B360A-13-F; D_SMA
D8: LTST-C190KGKT; LED_0603_1608Metric
F1, F2: MF-MSMF014/60X-2; Bourns_MF-MSMF_1812_Style2
H1, H2, H3, H4: M3; MountingHole_3.2mm_M3
J1: XT60PW-M; AMASS_XT60PW-M_1x02_P7.20mm_Horizontal
J2: XT60PW-F; AMASS_XT60PW-F_1x02_P7.20mm_Horizontal
J3: JST XH 4-pin; JST_XH_B4B-XH-A_1x04_P2.50mm_Vertical
J4: CIRCUIT_ID; PinHeader_1x02_P2.54mm_Vertical
J5, J6, J8: JST XH 3-pin; JST_XH_B3B-XH-A_1x03_P2.50mm_Vertical
J7: CAN_TERM; PinHeader_1x02_P2.54mm_Vertical
J9: 3V3 | VIO | 5V; PinHeader_1x03_P2.54mm_Vertical
J10, J11: 1x9 socket; PinSocket_1x09_P2.54mm_Vertical_NoPads
L1: 10µH; L_Bourns_SRN6045TA
LOGO**: PunderWorks_Logo_14mm
Q1, Q2: CSD18532Q5B | VSON-CLIP-8 5x6mm (DNK); TDSON-8-1
Q3: MMBT3904; SOT-23
Q4, Q5, Q6, Q7: BSS138; SOT-23
R1: 2.2kΩ; R_0603_1608Metric
R2, R26, R30: 1kΩ; R_0603_1608Metric
R3, R11: 47kΩ; R_0603_1608Metric
R4, R6: 33kΩ; R_0603_1608Metric
R5, R7, R9, R15, R20, R23, R24, R25, R27: 10kΩ; R_0603_1608Metric
R8: 180kΩ; R_0603_1608Metric
R10, R12, R14, R17, R18: 100kΩ; R_0603_1608Metric
R13: 1mΩ; R_2512_6332Metric
R16: 3.3Ω; R_1206_3216Metric
R19: 56.2kΩ; R_0603_1608Metric
R21, R22, R29, R31, R32: 4.7kΩ; R_0603_1608Metric
R28: 120Ω; R_0805_2012Metric
SH1, SH2, SH3: Jumper shunt for 2.54mm PinHeader; BOM_Only_JumperShunt
U1: LM5060MM/NOPB; TSSOP-10_3x3mm_P0.5mm
U2: INA237; TSSOP-10_3x3mm_P0.5mm
U3: LMR14030SDDAR | HSOIC-8 PowerPAD (DDA); TI_SO-PowerPAD-8_ThermalVias
U4: ESP32-C5-Zero-M; Waveshare_ESP32-C5-Zero-M_Socketed
U5: TCAN334G; SOIC-8_3.9x4.9mm_P1.27mm

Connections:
+3V3: C4.1, C14.1, C15.1, J9.1, Q6.1, Q7.1, R21.2, R22.2, R23.2, R24.2, R25.2, R26.1, R27.2, R29.2, R31.2, U2.6, U4.3, U5.3
+5V: C11.1, C12.1, C13.1, J3.4, J9.3, L1.2, R19.1, U4.1
BUCK_BOOT: C10.1, U3.1
BUCK_EN: R17.2, U3.3
BUCK_FB: R19.2, R20.1, U3.5
BUCK_RT: R18.1, U3.4
BUCK_SS: C9.1, U3.6
BUCK_SW: C10.2, D7.1, L1.1, U3.8
BUCK_VIN: C6.1, C7.1, C8.1, R16.2, R17.1, U3.2
CANH: J5.3, J6.3, R28.1, U5.7
CANL: J5.2, J6.2, J7.2, U5.6
CAN_GND: F1.1, J5.1, J6.1
CAN_RX: U4.13, U5.4
CAN_TX: U4.12, U5.1
CIRCUIT_ID: J4.1, R25.1, U4.11
GATE_C: C2.1, R2.2
GATE_DRV: D3.1, R1.1, U1.10
GATE_FET: D3.2, Q1.4, Q2.4, Q3.3, R1.2, R2.1
GND: C1.2, C2.2, C3.2, C4.2, C5.2, C6.2, C7.2, C8.2, C9.2, C11.2, C12.2, C13.2, C14.2, C15.2, D1.2, D5.2, D6.2, D7.2, D8.1, F1.2, F2.2, J1.1, J2.1, J4.2, Q4.2, Q5.2, R3.2, R7.2, R9.2, R11.2, R12.2, R15.2, R18.2, R20.2, U1.6, U2.1, U2.2, U2.7, U3.7, U3.9, U4.2, U5.2
I2C_SCL: R22.1, U2.5, U4.7
I2C_SDA: R21.1, U2.4, U4.6
INA_ALERT: R23.1, U2.3, U4.8
unnamed: J7.1, R28.2
PROT_EN: Q4.3, R10.2, R11.1, U1.5
PROT_OUT: R5.2, U1.9
PROT_OVP: R8.2, R9.1, U1.3
PROT_SENSE: R4.2, U1.1
PROT_TIMER: C3.1, U1.7
PROT_UVLO: R6.2, R7.1, U1.4
PWR_CUTOFF: Q4.1, R12.1, U4.5
PWR_LED_A: D8.2, R26.2
PWR_PGOOD: R24.1, U1.8, U4.4
REV_BASE: D4.1, Q3.1, R3.1
SW_LED_EN: Q5.1, R27.1, U4.17
SW_LED_K: J3.3, Q5.3
UART_GND: F2.1, J8.1
UART_RX: J8.2, Q7.3, R32.2
UART_RX_3V3: Q7.2, R31.1, U4.14
UART_TX: J8.3, Q6.3, R30.2
UART_TX_3V3: Q6.2, R29.1, U4.9
UART_VIO: J9.2, R30.1, R32.1
VBAT_ADC: C5.1, R14.2, R15.1, U4.10
VBAT_IN: D1.1, J1.2, J3.1, Q1.5, R4.1
VOUT: D5.1, D6.1, J2.2, R13.2, U2.8, U2.9
VSW_CTRL: C1.1, D2.1, R6.1, R8.1, R10.1, R14.1, R16.1, U1.2
VSW_MID: D4.2, Q1.1, Q1.2, Q1.3, Q2.1, Q2.2, Q2.3, Q3.2
VSW_OUT: Q2.5, R5.1, R13.1, U2.10
VSW_RAW: D2.2, J3.2

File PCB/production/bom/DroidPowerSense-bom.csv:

Refs,Quantity,Value,Footprint,MF,MPN,LCSC,Mouser,DigiKey,Hand,DNP
"R10,R12,R14,R17,R18","5","100kΩ","Resistor_SMD:R_0603_1608Metric","YAGEO","RC0603FR-07100KL","C14675","603-RC0603FR-07100KL","311-100KHRCT-ND","",""
"C1,C10,C13,C14,C15,C2,C4,C5,C8","9","100nF","Capacitor_SMD:C_0603_1608Metric","Murata Electronics","GRM188R72A104KA35D","C77058","81-GRM188R72A104KA35","490-3285-1-ND","",""
"R15,R20,R23,R24,R25,R27,R5,R7,R9","9","10kΩ","Resistor_SMD:R_0603_1608Metric","YAGEO","RC0603FR-0710KL","C98220","603-RC0603FR-0710KL","311-10.0KHRCT-ND","",""
"C9","1","10nF","Capacitor_SMD:C_0603_1608Metric","Samsung Electro-Mechanics","CL10B103KB8NNNC","C1589","187-CL10B103KB8NNNC","1276-1009-1-ND","",""
"C11,C12,C6,C7","4","10µF","Capacitor_SMD:C_1206_3216Metric","Samsung Electro-Mechanics","CL31A106KBHNNNE","C13585","187-CL31A106KBHNNNE","1276-2876-1-ND","",""
"L1","1","10µH","Inductor_SMD:L_Bourns_SRN6045TA","Bourns","SRN6045TA-100M","C2046332","652-SRN6045TA-100M","SRN6045TA-100MCT-ND","",""
"R28","1","120Ω","Resistor_SMD:R_0805_2012Metric","YAGEO","RC0805FR-07120RL","C114245","603-RC0805FR-07120RL","311-120CRCT-ND","",""
"R8","1","180kΩ","Resistor_SMD:R_0603_1608Metric","YAGEO","RC0603FR-07180KL","C123419","603-RC0603FR-07180KL","311-180KHRCT-ND","",""
"D4","1","1N4148W-TP","Diode_SMD:D_SOD-123","Micro Commercial Components","1N4148W-TP","C77978","833-1N4148W-TP","1N4148W-TPMSCT-ND","",""
"R2,R26,R30","3","1kΩ","Resistor_SMD:R_0603_1608Metric","YAGEO","RC0603FR-071KL","C22548","603-RC0603FR-071KL","311-1.00KHRCT-ND","",""
"R13","1","1mΩ","Resistor_SMD:R_2512_6332Metric","Bourns","CSS2H-2512R-1L00F","C4175647","652-CSS2H-2512R1L00F","CSS2H-2512R-1L00FCT-ND","",""
"J10,J11","2","1x9 socket","DroidPowerSense:PinSocket_1x09_P2.54mm_Vertical_NoPads","Sullins Connector Solutions","PPPC091LFBN-RC","C5362844","","S7042-ND","Yes","Yes"
"R1","1","2.2kΩ","Resistor_SMD:R_0603_1608Metric","YAGEO","RC0603FR-072K2L","C114662","603-RC0603FR-072K2L","311-2.20KHRCT-ND","",""
"C3","1","2.2µF","Capacitor_SMD:C_0603_1608Metric","Samsung Electro-Mechanics","CL10A225KO8NNNC","C23630","187-CL10A225KO8NNNC","1276-1119-1-ND","",""
"R16","1","3.3Ω","Resistor_SMD:R_1206_3216Metric","YAGEO","RC1206FR-073R3L","C137283","603-RC1206FR-073R3L","311-3.30FRCT-ND","",""
"R4,R6","2","33kΩ","Resistor_SMD:R_0603_1608Metric","YAGEO","RC0603FR-0733KL","C126359","603-RC0603FR-0733KL","311-33.0KHRCT-ND","",""
"J9","1","3V3 | VIO | 5V","Connector_PinHeader_2.54mm:PinHeader_1x03_P2.54mm_Vertical","Würth Elektronik","61300311121","C2915006","710-61300311121","732-5316-ND","Yes","Yes"
"R21,R22,R29,R31,R32","5","4.7kΩ","Resistor_SMD:R_0603_1608Metric","YAGEO","RC0603FR-074K7L","C99782","603-RC0603FR-074K7L","311-4.70KHRCT-ND","",""
"R11,R3","2","47kΩ","Resistor_SMD:R_0603_1608Metric","YAGEO","RC0603FR-0747KL","C105579","603-RC0603FR-0747KL","311-47.0KHRCT-ND","",""
"R19","1","56.2kΩ","Resistor_SMD:R_0603_1608Metric","YAGEO","RC0603FR-0756K2L","C482887","603-RC0603FR-0756K2L","311-56.2KHRCT-ND","",""
"D2,D3","2","B160-13-F","Diode_SMD:D_SMA","Diodes Incorporated","B160-13-F","C24784","621-B160-F","B160-FDICT-ND","",""
"D7","1","B360A-13-F","Diode_SMD:D_SMA","Diodes Incorporated","B360A-13-F","C94193","621-B360A-F","B360A-FDICT-ND","",""
"D5","1","B560C-13-F","Diode_SMD:D_SMC","Diodes Incorporated","B560C-13-F","C85100","621-B560C-F","B560C-FDICT-ND","",""
"Q4,Q5,Q6,Q7","4","BSS138","Package_TO_SOT_SMD:SOT-23","Diodes Incorporated","BSS138-7-F","C40912","621-BSS138-7-F","BSS138-7-FDICT-ND","",""
"J7","1","CAN_TERM","Connector_PinHeader_2.54mm:PinHeader_1x02_P2.54mm_Vertical","Würth Elektronik","61300211121","C2915055","710-61300211121","732-5315-ND","Yes","Yes"
"J4","1","CIRCUIT_ID","Connector_PinHeader_2.54mm:PinHeader_1x02_P2.54mm_Vertical","Würth Elektronik","61300211121","C2915055","710-61300211121","732-5315-ND","Yes","Yes"
"Q1,Q2","2","CSD18532Q5B | VSON-CLIP-8 5x6mm (DNK)","Package_TO_SOT_SMD:TDSON-8-1","Texas Instruments","CSD18532Q5B","C882766","595-CSD18532Q5B","296-42322-1-ND","",""
"U4","1","ESP32-C5-Zero-M","DroidPowerSense:Waveshare_ESP32-C5-Zero-M_Socketed","Waveshare","ESP32-C5-Zero-M","","","","Yes","Yes"
"U2","1","INA237","Package_SO:TSSOP-10_3x3mm_P0.5mm","Texas Instruments","INA237AIDGSR","C2864837","595-INA237AIDGSR","296-INA237AIDGSRCT-ND","",""
"J5,J6,J8","3","JST XH 3-pin","Connector_JST:JST_XH_B3B-XH-A_1x03_P2.50mm_Vertical","JST","B3B-XH-A(LF)(SN)","C144394","306-B3BXHALFSNP","","Yes","Yes"
"J3","1","JST XH 4-pin","Connector_JST:JST_XH_B4B-XH-A_1x04_P2.50mm_Vertical","JST","B4B-XH-A(LF)(SN)","C144395","306-B4BXHALFSN","","Yes","Yes"
"SH1,SH2,SH3","3","Jumper shunt for 2.54mm PinHeader","DroidPowerSense:BOM_Only_JumperShunt","Würth Elektronik","60900213421","","710-60900213421","732-2678-ND","Yes","Yes"
"U1","1","LM5060MM/NOPB","Package_SO:TSSOP-10_3x3mm_P0.5mm","Texas Instruments","LM5060MM/NOPB","C74456","926-LM5060MM/NOPB","LM5060MM/NOPBCT-ND","",""
"U3","1","LMR14030SDDAR | HSOIC-8 PowerPAD (DDA)","Package_SO:TI_SO-PowerPAD-8_ThermalVias","Texas Instruments","LMR14030SDDAR","C182078","595-LMR14030SDDAR","296-42492-1-ND","",""
"D8","1","LTST-C190KGKT","LED_SMD:LED_0603_1608Metric","Lite-On","LTST-C190KGKT","C125094","859-LTST-C190KGKT","160-1435-1-ND","",""
"F1,F2","2","MF-MSMF014/60X-2","DroidPowerSense:Bourns_MF-MSMF_1812_Style2","Bourns","MF-MSMF014/60X-2","","652-MF-MSMF014/60X-2","118-MF-MSMF014/60X-2CT-ND","",""
"Q3","1","MMBT3904","Package_TO_SOT_SMD:SOT-23","onsemi","MMBT3904LT1G","C81464","863-MMBT3904LT1G","MMBT3904LT1GOSCT-ND","",""
"D6","1","SMBJ33CA-13-F","Diode_SMD:D_SMB","Diodes Incorporated","SMBJ33CA-13-F","C135068","621-SMBJ33CA-F","SMBJ33CA-FDICT-ND","",""
"D1","1","SMCJ33CA-13-F","Diode_SMD:D_SMC","Diodes Incorporated","SMCJ33CA-13-F","C135163","621-SMCJ33CA-F","SMCJ33CA-FDICT-ND","",""
"U5","1","TCAN334G","Package_SO:SOIC-8_3.9x4.9mm_P1.27mm","Texas Instruments","TCAN334GDR","C189939","595-TCAN334GDR","296-43570-1-ND","",""
"J2","1","XT60PW-F","DroidPowerSense:AMASS_XT60PW-F_1x02_P7.20mm_Horizontal","Amass","XT60PW-F","C428722","","4786-XT60PW-F-ND","Yes","Yes"
"J1","1","XT60PW-M","DroidPowerSense:AMASS_XT60PW-M_1x02_P7.20mm_Horizontal","Amass","XT60PW-M","C98732","","4786-XT60PW-M-ND","Yes","Yes"

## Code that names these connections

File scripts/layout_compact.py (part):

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    "R19": (80.6, 82.4, 0.0),     # SDA pull-up
    "R20": (80.6, 84.4, 0.0),     # SCL pull-up
    "R21": (80.6, 86.4, 0.0),     # ALERT pull-up
    "R25": (89.4, 72.4, 0.0),     # SW_LED_EN pull-up (module pin 17)
    "R23": (89.4, 85.0, 0.0),     # CIRCUIT_ID pull-up (module pin 11)
    "R13": (86.0, 87.4, 0.0),     # VBAT ADC top
    "R14": (89.4, 87.4, 0.0),     # VBAT ADC bottom
    "C4": (89.4, 89.4, 0.0),      # VBAT ADC filter
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    "VOUT": (92.8, 46.9, 112.0, 55.6),      # R12 pad 2, D6, D5, J2 +
}
# Q1 sources to Q2 sources: F.Cu only (1.8 mm, ~0.1 mOhm). The gap between the FETs is too narrow
# for a via, and keeping it off B.Cu leaves room for the GATE_FET link to cross there.
VSW_MID_POUR = (77.0, 48.6, 81.0, 54.0)
# In2.Cu supply planes below the power row (priority 2).
IN2_PLANES = {
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    label("CIRCUIT ID", 103.0, 64.6)
    label("NO JUMPER = 1", 103.0, 66.0)
    label("JUMPER ON = 2", 103.0, 67.4)
    # CAN: J5 in, J6 out (pin 2 CANH above pin 1 CANL)
    label("CAN IN", 119.5, 70.9, R)
    label("CAN OUT", 119.5, 89.2, R)
    for y_h, y_l in ((74.5, 77.0), (83.0, 85.5)):
        label("CANH", 112.9, y_h, R)
        label("CANL", 112.9, y_l, R)
    label("TERM", 104.5, 70.6)   # J7: CAN 120R terminator jumper
    # UART: J8 on the bottom edge (pin 1 RX at x 101.5, pin 2 TX at x 104.0), J9 VIO select
    label("RX", 98.3, 92.45, R)
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    # VBUS (VOUT): Bridge U2.9 to U2.8
    add_track_path(board, "VOUT", [(89.9, 56.45), (90.4, 56.45)], width_mm=0.25, layer_name="F.Cu")

    # ── LM5060 VSW_OUT Sense (R4.1) on F.Cu stepping east of R4.2 / PROT_OUT ──
    add_track_path(board, "VSW_OUT", [(87.0, 62.025), (88.2, 62.025), (88.2, 53.0), (87.438, 51.3)], width_mm=0.25, layer_name="F.Cu")

    add_track_path(board, "VOUT", [(93.362, 51.3), (96.7, 54.05), (102.5, 53.6), (108.5, 51.3)], width_mm=2.5, layer_name="F.Cu")
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    add_track_path(board, "PROT_EN", [(79.85, 67.8), (70.0, 67.8), (70.0, 69.0)], width_mm=0.25, layer_name="In2.Cu")
    add_via(board, "PROT_EN", 70.0, 69.0)
    add_track_path(board, "PROT_EN", [(68.825, 69.0), (71.175, 69.0)], width_mm=0.25, layer_name="F.Cu")
    # Branch to Q4.3 stepping east of PWR_CUTOFF via
    add_track_path(board, "PROT_EN", [(79.85, 67.8), (81.938, 69.5), (81.938, 73.0)], width_mm=0.25, layer_name="In2.Cu")
    add_via(board, "PROT_EN", 81.938, 73.0)

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
def route_remote_switch(board: pcbnew.BOARD) -> None:
    """Route remote switch indicator LED drive and cathode."""
    # SW_LED_K: J3.3 (55.5, 79.0) to Q5.3 (55.438, 86.9) stepping around J3.4 (+5V)
    add_track_path(board, "SW_LED_K", [(55.5, 79.0), (57.2, 79.0), (57.2, 85.5), (55.438, 85.5), (55.438, 86.9)], width_mm=0.35, layer_name="F.Cu")

    # SW_LED_EN: U4.17 (92.62, 72.43) to R25.1 (88.575, 72.4) and Q5.1 (53.562, 85.95)
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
